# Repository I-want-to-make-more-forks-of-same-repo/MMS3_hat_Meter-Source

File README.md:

# MMS3 Hat Meter Source

## Sekcja 1: Dokumentacja Hat'a

### Krótki opis projektu
Hat meter-source to hat z woltomierzem, amperemoierzem, źródłem prądowym, napięciowym, obciążeniem napięciowym, prądowym (i pewnie też mocowym) na 1 kanale. Aktualnie płytka ma na celu przetestowanie konceptu i jest prototypem

### Zgodność ze standardem ChainBus

* ✅ Używa złącza ChainBus, nie zmienia jego miejsca ani pinoutu.
* ✅ Używa wyłącznie interfejsów I2C, SPI lub UART i nie inicjuje samodzielnie nowych transmisji (Nie jest master'em I2C albo SPI).
* ✅ Spełnia wymagania mechaniczne standardu (wymiary PCB, rozstaw otworów).
* ✅ Pobiera maksymalny prąd zgodny z ilością na jednego hat'a **-> Ma złącze XT60**
* ❌ Obsługuje napięcie wejściowe BRD_VIN do wartości 48V. **-> 12V max**

### Komunikacja i adresowanie

#### Magistrala Chainbus  I2C
Poniższa tabela przedstawia adresację urządzeń na magistrali I2C.

| Układ (IC)   | Funkcja                 |     Address     |
| :----------- | :---------------------- | :-------------: |
| **CH32V003** | Główny kontroler płytki | `Programowalny` |

#### Magistrala Chainbus SPI
Brak

#### Magistrala Chainbus UART
Brak

### Pinout złączy

| Jn     | Co                              | Jaki pin co robi                        |
| :----- | :------------------------------ | :-------------------------------------- |
| **J6** | Wyjście/wejście miernika/źródła | Pin 1: + <br>Pin 2: -                   |
| **J8** | TX UART z CH32V003              | Pin 1: TX (nazwany: free) <br>Pin 2: 0V |

Okay, i będe nazywał Pin + z J6 jako "Obciążenie" albo "Źródło" albo "Wejście" w dalszej części dokumentacji. To jest ten główny element tej płytki

### Wzmacniaczne operacyjne
Na płytce są użyte 4 wzmacniacze operacyjne

#### OpAmp Amperomierzy Wzmocniania Główny (OpAmp Amperomierzy)
Na schemacie to U3 kanał 1

| Pin  | Do czego podłączony                   |
| :--- | :------------------------------------ |
| +    | Wybrany bocznik prądowy (Sink/Source) |
| -    | Programowalny Rezystor Feedback       |
| OUT  | Amm_ADC (CH32 PD3)                    |

Programowalne wzmocnienie k

k = 31, jeśli Amm_Range_1 == 0

k = 70, jeśli Amm_Range_1 == 1

#### OpAmp Wzmocnienia amperomierza dla Mosfetów (OpAmp AmmMos)
Na schemacie to U6 kanał 1

| Pin  | Do czego podłączony                       |
| :--- | :---------------------------------------- |
| +    | Wybrany bocznik prądowy (Sink/Source)     |
| -    | Stały Rezystor Feedback                   |
| OUT  | Mosfet_Feedback jeśli Sel_Output_amm == 1 |

Stałe wzmocnienie = 11

Note: Wybrany bocznik prądowy jest ten sam dla obu OpAmp'ów. Nie możesz mieć jednego na jednym i drugiego na drugim

Note: Oba boczniki prądowe mają 20mΩ

#### OpAmp Mosfeta N
Na schemacie to U3 kanał 2

| Pin  | Do czego podłączony |
| :--- | :------------------ |
| +    | PWM_N z filtrem RC  |
| -    | Mosfet_Feedback     |
| OUT  | Bramka NMos'a       |

#### OpAmp Mosfeta P
Na schemacie to U7 kanał 2

| Pin  | Do czego podłączony |
| :--- | :------------------ |
| +    | Mosfet_Feedback     |
| -    | PWM_P z filtrem RC  |
| OUT  | Bramka PMos'a       |

Mosfet'y P są logicznie odwrócone od N, dlatego  mają na odwrót podłączenia + -

### Pinout CH32
| Pin            | Net name z kicad'a   | Co robi                                                                                      |
| :------------- | :------------------- | :------------------------------------------------------------------------------------------- |
| **PC0**        | PWM_P                | Sygnał PWM do wejścia OpAmp'a PMos'a                                                         |
| **PC1 (SDA)**  | N/A                  | SDA do ChainBus'a                                                                            |
| **PC2 (SCL)**  | N/A                  | SCL do ChainBus'a                                                                            |
| **PC3**        | Sel_Output_amm       | Wybór sprzężenia zwrotnego OpAmp'a PMos i Nmos - Na wyjście OpAmp'a AmmMos                   |
| **PC4**        | Sel_Output_Volt      | Wybór sprzężenia zwrotnego OpAmp'a PMos i Nmos - Na dzielnik napięcia 0.2 * Napięcie wejścia |
| **PC5 (SCK)**  | Amm_Range_1          | Wybór programowalnego wzmocnianie OpAmp'a Amperomierzy                                       |
| **PC6 (MOSI)** | Sel_Amp_Source       | Wybór wejscia dla OpAmp AmmMos i Amperomierzy na prąd wchodzący do pinu '+' Wejścia (Source) |
| **PC7 (MISO)** | Sel_Amp_Sink         | Wybór wejscia dla OpAmp AmmMos i Amperomierzy na prąd wychodzący z pinu '+' Wejścia (Sink)   |
| **PD0**        | Volt_Range1          | Wybór programowalnego dzielnika napięcia dla Volt_ADC                                        |
| **PD1**        | N/A                  | SWIO, programowanie MCU                                                                      |
| **PD2**        | PWM_N                | Sygnał PWM do wejścia OpAmp'a NMos'a                                                         |
| **PD3**        | Amm_ADC              | Kanał ADC połączony z wyjściem OpAmp'a Amperomierzy                                          |
| **PD4**        | Volt_ADC             | Kanał ADC połączony z programowalnym dzielnikiem napięcie Wejścia                            |
| **PD5 (TX)**   | Free                 | Wolny pin, do użycia jako dioda debug lub TX UART'a CH32V003                                 |
| **PD6 (RX)**   | Lmao1                | Wybór sprzężenia zwrotnego OpAmp'a - Na stałe 1.65V                                          |
| **PD7 (NRST)** | *NC (niepodłączony)* | NC                                                                                           |

Note: żeby Sel_Output_Volt, Sel_Output_amm i lmao1 działały potrzeba zewrzeć odpowiednio zworki J9 J10 J11

Note: Zwieraj je jedna na raz, bo jak kilka zewrzesz na Mosfet_Feedback będzie takie jak na najwyższym napięciu z podłączonych zworek

### Konfiguracja układu (Zworki/Rezystory)

| Co      | Jak podłączone                    | Efekt                                                                                             |
| :------ | :-------------------------------- | :------------------------------------------------------------------------------------------------ |
| **R15** | R15 Wylutowane <br> R15 Wlutowane | J6 '-' niepodłączony <br> J6 '-' podłączony do GND                                                |
| **R16** | R16 Wylutowane <br> R16 Wlutowane | Bramka Pmos'a podłączona do VIN_ChainBus <br> Bramka Pmos'a podłączona do wyjścia swojego OpAmp'a |
| **R26** | R26 Wylutowane <br> R26 Wlutowane | Bramka Nmos'a podłączona do 0V <br> Bramka Nmos'a podłączona do wyjścia swojego OpAmp'a           |
| **R27** | R27 Wylutowane <br> R27 Wlutowane | Dolna część mostka H odłączona <br> Dolna część mostka H podłączona do GND                        |
| **R29** | R29 Wylutowane <br> R29 Wlutowane | Wejście '-' OpAmp'a NMos'a floating <br> Wejście '-' OpAmp'a NMos'a podłączone do Mosfet_Feedback |
| **R30** | R30 Wylutowane <br> R30 Wlutowane | Wejście '+' OpAmp'a NMos'a floating <br> Wejście '+' OpAmp'a NMos'a podłączone do PWM_N przez RC  |
| **R32** | R32 Wylutowane <br> R32 Wlutowane | Wejście '-' OpAmp'a PMos'a floating <br> Wejście '-' OpAmp'a PMos'a podłączone do PWM_P przez RC  |
| **R42** | R42 Wylutowane <br> R42 Wlutowane | Wejście '+' OpAmp'a PMos'a floating <br> Wejście '+' OpAmp'a PMos'a podłączone do Mosfet_Feedback |
| **J9**  | J9 Rozwarte <br> J9 Zwarte        | Sel_Output_Volt nie działa jest elektrycznie odłączone <br> Można używać Sel_Output_Volt          |
| **J10** | J10 Rozwarte <br> J10 Zwarte      | Sel_Output_amm nie działa jest elektrycznie odłączone <br> Można używać Sel_Output_amm            |
| **J11** | J11 Rozwarte <br> J11 Zwarte      | Lmao1 nie działa jest elektrycznie odłączone <br> Można używać Lmao1                              |

Bascially rezystorów nie trzeba ruszać, chyba że chcesz wyłączyć któraś połowe mostka H, a zworki chcesz mieć tylko jedną na raz podpiętą jak zaczynasz programować.

### Szczegółowy opis
Na Hat'ie jest
- 1 Kanał woltomierza o programowalnym dzielniku napięcia
- 1 Kanał amperomierza o programowalnym wzmocnieniu oraz wybieralnym wejściu (między mierzeniem prądu sink a source)
- 1 Półmostek H

Do złącza J6 można podłączyć obciążenie/źródło i mierzyć prąd/napięcie na nim lub zasilać/obciążać go programowalnie. Minus (pin 1) tego złacza jest zwarty do masy układu, a plus (pin 2) jest podłączony do półmostka H.

Można mierzyć napięcie na **Wejściu** (J6 Pin 2). Napięcie **Wejścia** jest podłączone przez programowalny dzielnik napięciea do kanału ADC CH32V003 (Volt_ADC, PD4). Programowalny dzielnik napięcie zmienia się przez konfiguracje Volt_Range1

| Stan Volt_Range1 | napięcie na Volt_ADC        |
| :--------------- | :-------------------------- |
| High             | 0.2 * Napięcie Wejściowe    |
| Low              | 0.4285 * Napięcie Wejściowe |

Można mierzyć prąd na **Wejściu**. W tym celu na początku należy wybrać który prąd chcemy mierzyć
- Sel_Amp_Source - Prąd który płynie od '-' wyjścia do GND (Do amperomierza, i programowalnego źródła)
- Sel_Amp_Sink - Prąd który płynie od +, przez Mostek H do GND (Do Programable load)

Tryb pomiaru prądu (Sink, Source) jest wybrany dla pomiaru prądu przez mikrokontroler oraz dla OpAmp AmmMos (Sprzęrzenia zwrotnego OpAmp'ów Mosfetów). Pomiar prądu odbywa się przez rezystory 20mΩ. Napięcie na tym rezystorze jest wzmocnione. OpAmp AmmMos ma stałe wzmocnienie = 11 a mikrokontroler programowalne przez Amm_Range_1.

| Stan Amm_Range_1 | napięcie na Amm_ADC |
| :--------------- | :------------------ |
| High             | 71 * Prąd * 0.02    |
| Low              | 31 * Prąd * 0.02    |

Sterowanie półmostkiem H odbywa się pośrednio przez PWM z mikrokontrolera. Pośrednio, bo PWM jest wygładzane filtrem RC i idzie do wzmacniacza operacyjnego. Tak to wygląda:

PWM z MCU (PWM_N albo PWM_H) -> Filtr dolnoprzepustowty RC który z PWM robi stałe napięcie = 3.3 * % PWM -> Feedback Op Amp'a

Wzmacniacz operacyjny porównuje to wygładzone PWM z jedną z kilku programowo wybieranych opcji (Sel_Output_Volt, Sel_Output_amm, Lmao1) W celu zaimplementowanie closed loop control

| Co ma HIGH      | Do czego podpięty jest Mosfet_Feedback | Co można zaimplementować              |
| :-------------- | :------------------------------------- | ------------------------------------- |
| Sel_Output_Volt | 0.2 *          Napięcie Wejściowe      | Constant voltage source/sink          |
| Sel_Output_amm  | 11 * Prąd * 0.02                       | Constant current source/sink          |
| Lmao1           | 1.65V                                  | Sam amperomierz/woltomierz. Debugging |

Filtr RC składa się z 1kΩ i 1uF

Wszystkie Piny CH32V003 zostały wyprowadzone na Led'y w celu ułatwienia debuggowania. Oby to nie sprawiło problemów bo przez to są weak pulldown

### Tryby pracy
Jeśli jesteś programistą, to spoko gdyby udało ci się coś takiego zaimplementować

- Mierzenie napięcia
- Mierzenie prądu
- Źródło Prądowe
- Źródło Napięciowe
- Programowalne obciążenie Prądowe
- Programowalne obciążenie Napięciowe
- Programowalne obciążenie Mocowe

Która z tych opcji jest wybrana, wartości zmierzone albo nastawy muszą być konfigurowalne z poziomu MMS3, a nie Hat'a. I fajnie gdyby był jeden program na CH32 na wszystkie te tryby (One soft to rule them all ;)

I trzeba napisać oba: Software na CH32V003 i biblioteke hat'a żeby to działało ze sobą. Jak masz problem z CH32 to możesz debuggować WCH-Link'iem albo prinf'em (TX -> UART/USB przejściówka -> PC)

### Gotowe arkusze hierarchiczne
W projekcie zaprojektowano/użyto następujących arkuszy hierarchicznych:
* CH32V003

---

## Sekcja 2: Specyfikacja standardu ChainBus

### Architektura i łączenie modułów
Standard ChainBus umożliwia modułowe łączenie hatów. Na jednym MMS3 można zamontować pionowo **do 8 hat'ów**. Połączenie realizowane jest poprzez wpięcie złącza męskiego kolejnego hat'a w złącze żeńskie poprzedniego

### Komunikacja i sterowanie
Magistrala ChainBus jest w pełni cyfrowa. Płyta główna nie steruje bezpośrednio sygnałami ogólnego przeznaczenia (GPIO) na poszczególnych hat'ach. Wszelkie operacje (np. obsługa diod LED, odczyt krańcówek, generowanie sygnałów PWM) muszą być realizowane przez dedykowane układy scalone (np. ekspandery portów, sterowniki) komunikujące się przez interfejsy systemowe.

*Przykład:*
`MCU` $\rightarrow$ `Expander GPIO po I2C` $\rightarrow$ `Dioda LED`

Wybór aktywnego modułu realizowany jest przez układ przełącznika magistrali (bus switch) na płycie głównej. Dzięki temu linie I2C, SPI i UART są niezależne dla każdego hat'a (brak konfliktów adresów I2C między różnymi hatami).
* **Identyfikacja:** Każdy moduł powinien posiadać pamięć EEPROM na magistrali I2C w celu identyfikacji płyty przez system - układ M24C64-W skonfigurowany na adres `0x50` przy liniach adresowych A0, A1, A2 zwartych do masy.

### Zasilanie
Złącze ChainBus dostarcza następujące linie zasilania:

| Magistrala zasilania | Napięcie znamionowe | Maksymalny prąd (łączny dla 8 hatów) | Szacowany prąd na jeden hat |
| :------------------- | :-----------------: | :----------------------------------: | :-------------------------: |
| **5V**               |        5.0 V        |                1.0 A                 |           125 mA            |
| **12V stby**         |       12.0 V        |                0.5 A                 |            65 mA            |
| **BRD_VIN**          |   12.0 V – 48.0 V   |                1.5 A                 |           185 mA            |

*   Komponenty podłączone do linii `BRD_VIN` muszą być przystosowane do pracy z napięciem od 12V do **48 V**.
*   W przypadku zapotrzebowania na wyższą moc, dopuszczalne jest zastosowanie dodatkowego złącza zasilania XT60 (obciążalność do ok. 60 A).

### Wymagania mechaniczne i złącza
* **Wymiary PCB:** Niedozwolona jest zmiana obrysu płytki oraz położenia otworów montażowych, aby zachować kompatybilność mechaniczną.
* **Pozycjonowanie złączy ChainBus:** Położenie złącza standardu 2x16 SMD (raster 2.54 mm) musi być zgodne z szablonem. Złącze żeńskie montowane jest na stronie FRONT, natomiast złącze męskie na stronie BACK.
* **Interfejsy zewnętrzne:** Złącza wejścia/wyjścia (domyślnie standard JST-XH 2.5 mm o obciążalności do 3 A) oraz opcjonalne złącze XT60 powinny być umieszczone przy dolnej krawędzi płytki. Elementy regulacyjne i sygnalizacyjne (potencjometry, przełączniki, diody LED) należy lokalizować przy prawej krawędzi płytki.
* **Komponenty** Wszystkie komponenty powinny być na stronie front płytki żeby nie haczyły o elementy ze wcześniejszego hat'a

---

## Sekcja 3: Licencje

### Licencje projektu

*   **PCB:** CERN-OHL-P
*   **Software:** MIT License

[Template](https://github.com/KoNaR-Hefajstos/MMS3_hat_templates/) jest na licencji CC0 1.0 Universal. **Reszta projektu nie jest na tej licencji**

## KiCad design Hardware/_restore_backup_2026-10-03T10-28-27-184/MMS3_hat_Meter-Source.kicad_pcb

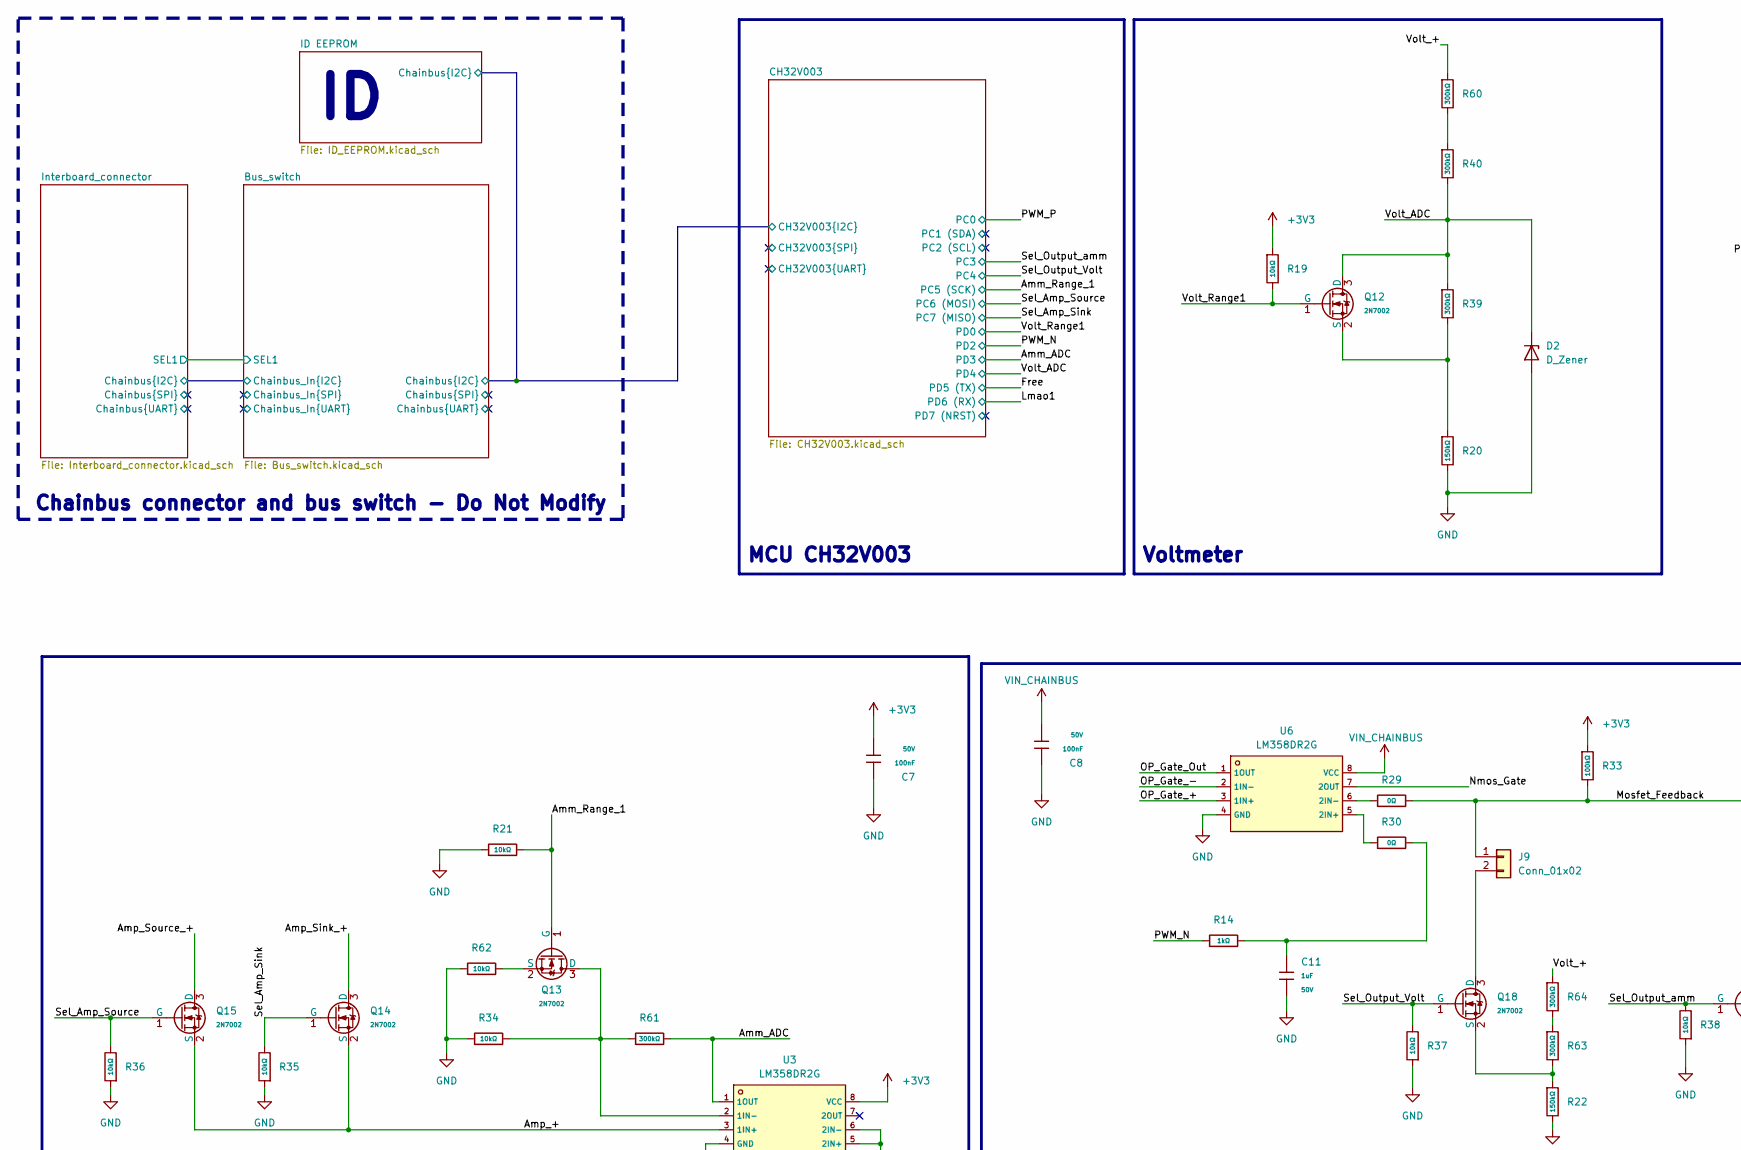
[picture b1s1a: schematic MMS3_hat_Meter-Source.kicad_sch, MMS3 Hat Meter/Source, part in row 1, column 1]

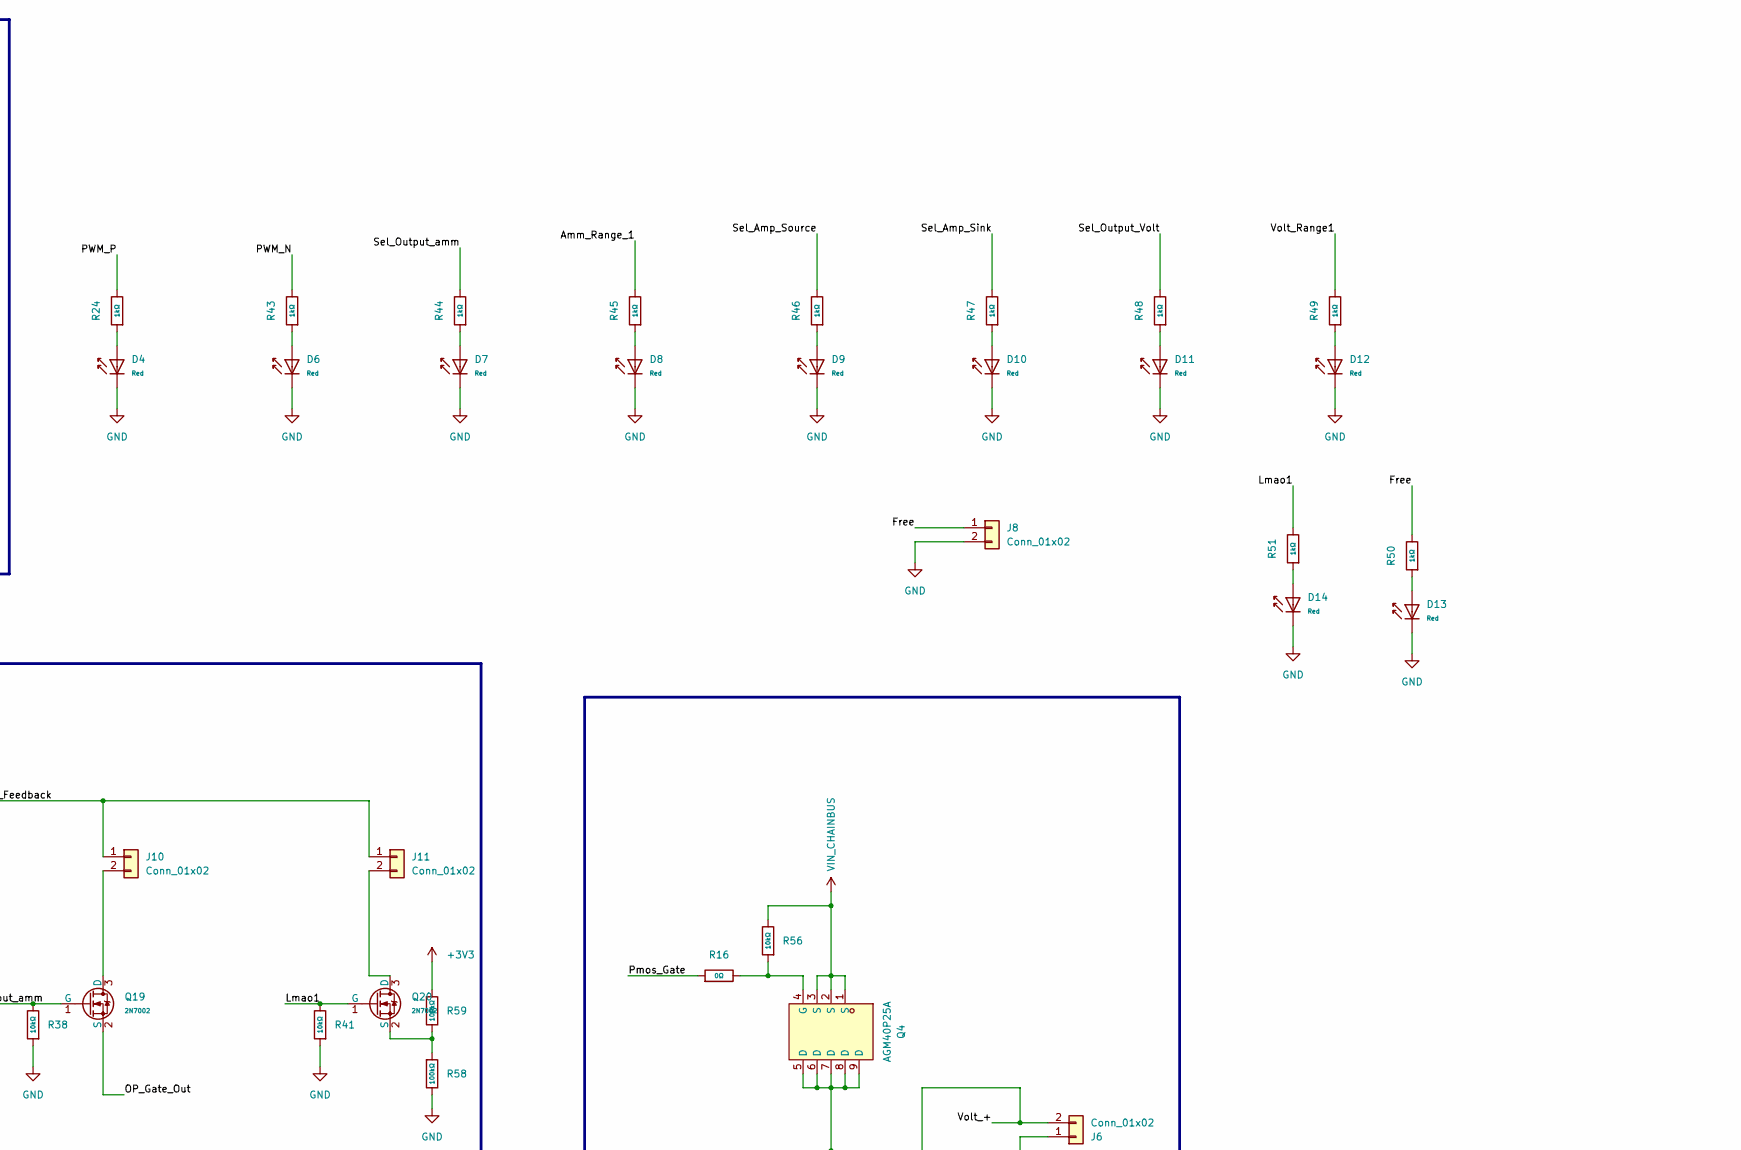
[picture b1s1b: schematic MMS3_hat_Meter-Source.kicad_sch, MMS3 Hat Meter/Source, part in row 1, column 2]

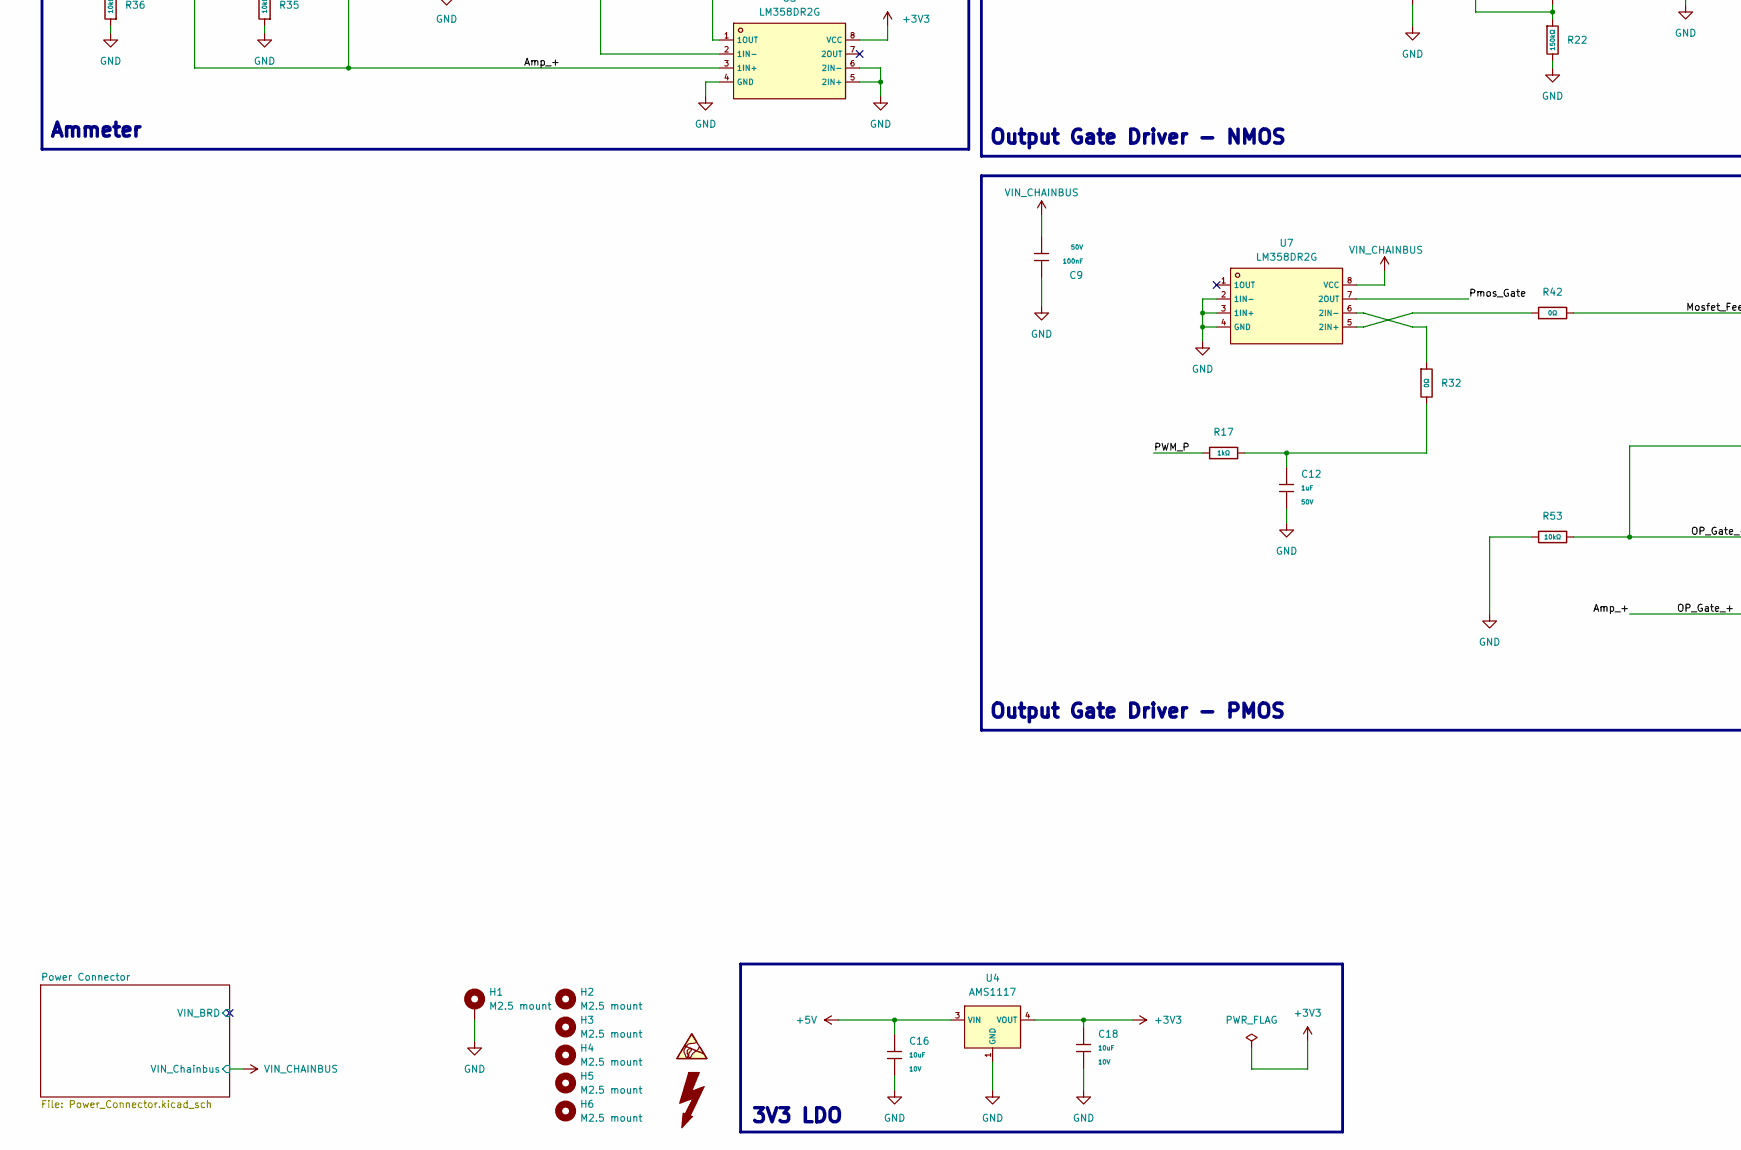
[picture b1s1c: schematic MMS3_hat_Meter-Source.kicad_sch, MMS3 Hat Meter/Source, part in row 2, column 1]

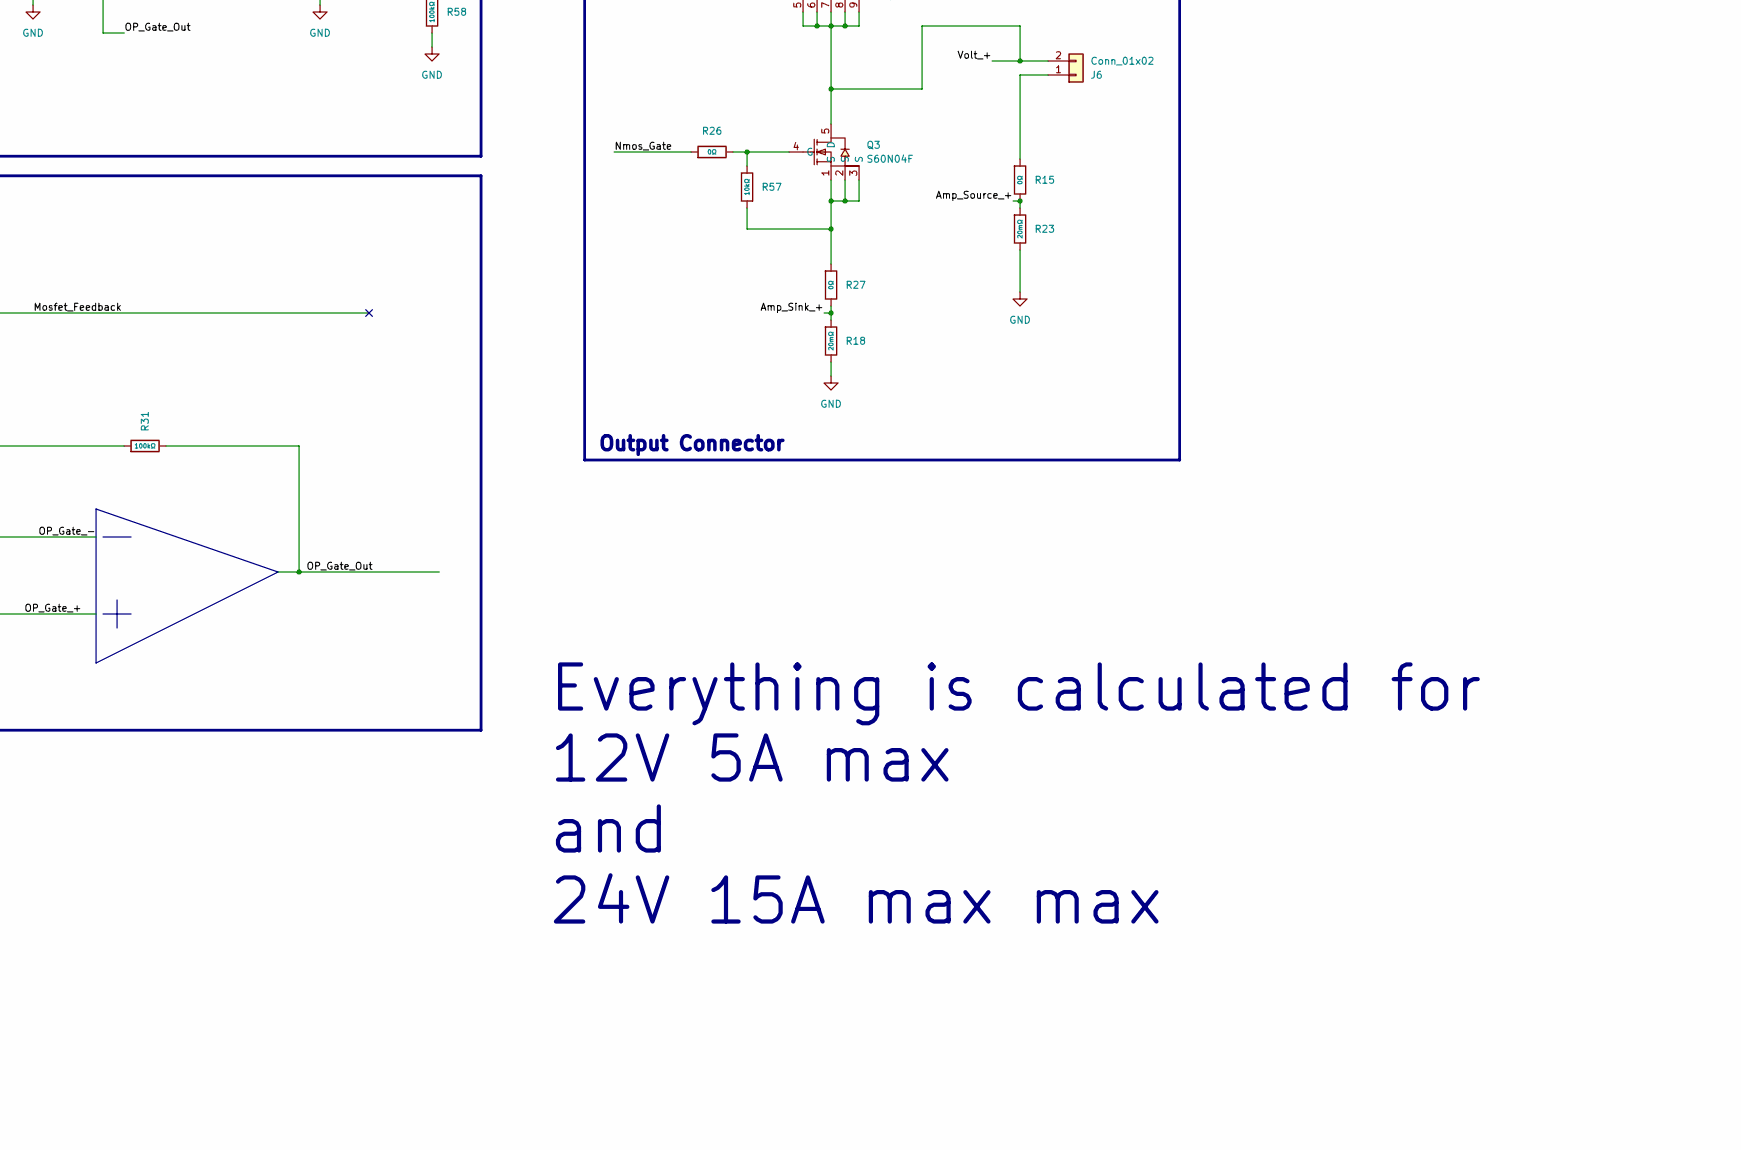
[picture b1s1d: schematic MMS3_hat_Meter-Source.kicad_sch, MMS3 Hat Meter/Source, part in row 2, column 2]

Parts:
C7, C8, C9: 100nF; C_0603; Voltage Rated 50V; Tolerance ±10%; Part CC0603KRX7R9BB104; LCSC C14663
C11, C12: 1uF; C_0603; Voltage Rated 50V; Tolerance ±10%; Part CL10A105KB8NNNC; LCSC C15849
C16, C18: 10uF; C_0603; Voltage Rated 10V; Tolerance ±10%; Part CL10A106KP8NNNC; LCSC C19702
D2: D_Zener; D_0603
D4, D6, D7, D8, D9, D10, D11, D12, D13, D14: Red; D_0603; Part KT-0603R; LCSC C2286
H1: M2.5 mount; MountingHole_2.7mm_M2.5_DIN965_Pad_TopOnly
H2, H3, H4, H5, H6: M2.5 mount; MountingHole_2.7mm_M2.5
J6: Conn_01x02; JST_XH_S2B-XH-A_1x02_P2.50mm_Horizontal
J8: Conn_01x02; JST_XH_B2B-XH-A_1x02_P2.50mm_Vertical
J9, J10, J11: Conn_01x02; PinHeader_1x02_P2.54mm_Vertical
Q3: S60N04F; DFN-5_L4.9-W5.9-P1.27-LS6.2-BL; MPN S60N04F; LCSC Part C7543820
Q4: AGM40P25A; PDFN-8_L5.8-W5.0-P1.27-LS6.1-BL; MPN AGM40P25A; LCSC Part C22386140
Q12, Q13, Q14, Q15, Q18, Q19, Q20: 2N7002; Q_SOT-23; Part 2N7002; LCSC C8545
R14, R17, R24, R43, R44, R45, R46, R47, R48, R49, R50, R51: 1kΩ; R_0603; Overload Voltage (Max) 75V; Tolerance ±1%; Part 0603WAF1001T5E; LCSC C21190
R15, R16, R26, R27, R29, R30, R32, R42: 0Ω; R_0603; Overload Voltage (Max) 75V; Tolerance ±1%; Part 0603WAF0000T5E; LCSC C21189
R18, R23: 20mΩ; R_0603; Overload Voltage (Max) 75V; Tolerance ±1%; Part 0603WAF100KT5E
R19, R21, R34, R35, R36, R37, R38, R41, R53, R56, R57, R62: 10kΩ; R_0603; Overload Voltage (Max) 75V; Tolerance ±1%; Part 0603WAF1002T5E; LCSC C25804
R20, R22: 150kΩ; R_0603; Overload Voltage (Max) 75V; Tolerance ±1%; Part 0603WAF1503T5E; LCSC C22807
R31, R33, R58, R59: 100kΩ; R_0603; Overload Voltage (Max) 75V; Tolerance ±1%; Part 0603WAF1003T5E; LCSC C25803
R39, R40, R60, R61, R63, R64: 300kΩ; R_0603; Overload Voltage (Max) 75V; Tolerance ±1%; Part 0603WAF3003T5E; LCSC C23024
U3, U6, U7: LM358DR2G; SOIC-8_L5.0-W4.0-P1.27-LS6.0-BL; Part LM358DR2G; LCSC C7950
U4: AMS1117; SOT-223-3_L6.5-W3.4-P2.30-LS7.0-BR; Output Voltage 3.3V; Dropout Voltage 1.3V@(800mA); Part AMS1117-3.3; LCSC C6186

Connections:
+3V3: C7.1, C18.1, R19.1, R33.1, R59.1, U3.8 (VCC), U4.2 (VOUT), U4.4 (VOUT); also elsewhere on the board
+5V: C16.1, U4.3 (VIN); also elsewhere on the board
/Amm_ADC: R61.2, U3.1 (1OUT); also elsewhere on the board
/Amm_Range_1: Q13.1 (G), R21.2, R45.2; also elsewhere on the board
/Amp_+: Q14.2 (S), Q15.2 (S), U3.3 (1IN+), U6.3 (1IN+)
/Amp_Sink_+: Q14.3 (D), R18.1, R27.2
/Amp_Source_+: Q15.3 (D), R15.2, R23.1
/Free: J8.1, R50.2; also elsewhere on the board
/Lmao1: Q20.1 (G), R41.2, R51.2; also elsewhere on the board
/Mosfet_Feedback: J9.1, J10.1, J11.1, R29.2, R33.2, R42.2
/Nmos_Gate: R26.1, U6.7 (2OUT)
/OP_Gate_-: R31.1, R53.1, U6.2 (1IN-)
/OP_Gate_Out: Q19.2 (S), R31.2, U6.1 (1OUT)
/PWM_N: R14.1, R43.2; also elsewhere on the board
/PWM_P: R17.1, R24.2; also elsewhere on the board
/Pmos_Gate: R16.1, U7.7 (2OUT)
/Sel_Amp_Sink: Q14.1 (G), R35.2, R47.2; also elsewhere on the board
/Sel_Amp_Source: Q15.1 (G), R36.2, R46.2; also elsewhere on the board
/Sel_Output_Volt: Q18.1 (G), R37.2, R48.2; also elsewhere on the board
/Sel_Output_amm: Q19.1 (G), R38.2, R44.2; also elsewhere on the board
/Volt_+: J6.2, Q3.5 (D), Q4.5 (D), Q4.6 (D), Q4.7 (D), Q4.8 (D), Q4.9 (D), R60.1, R64.1
/Volt_ADC: D2.1 (K), Q12.3 (D), R39.1, R40.2; also elsewhere on the board
/Volt_Range1: Q12.1 (G), R19.2, R49.2; also elsewhere on the board
GND: C7.2, C8.2, C9.2, C11.2, C12.2, C16.2, C18.2, D2.2 (A), D4.1, D6.1, D7.1, D8.1, D9.1, D10.1, D11.1, D12.1, D13.1, D14.1, H1.1 (1_1), J8.2, R18.2, R20.2, R21.1, R22.2, R23.2, R34.1, R35.1, R36.1, R37.1, R38.1, R41.1, R53.2, R58.2, R62.1, U3.4 (GND), U3.5 (2IN+), U3.6 (2IN-), U4.1 (GND), U6.4 (GND), U7.2 (1IN-), U7.3 (1IN+), U7.4 (GND); also elsewhere on the board
unnamed: C11.1, R14.2, R30.2
unnamed: C12.1, R17.2, R32.2
unnamed: D4.2, R24.1
unnamed: D6.2, R43.1
unnamed: D7.2, R44.1
unnamed: D8.2, R45.1
unnamed: D9.2, R46.1
unnamed: D10.2, R47.1
unnamed: D11.2, R48.1
unnamed: D12.2, R49.1
unnamed: D13.2, R50.1
unnamed: D14.2, R51.1
unnamed: J6.1, R15.1
unnamed: J9.2, Q18.3 (D)
unnamed: J10.2, Q19.3 (D)
unnamed: J11.2, Q20.3 (D)
unnamed: Q3.4 (G), R26.2, R57.2
unnamed: Q3.1 (S), Q3.2 (S), Q3.3 (S), R27.1, R57.1
unnamed: Q4.4 (G), R16.2, R56.1
unnamed: Q12.2 (S), R20.1, R39.2
unnamed: Q13.3 (D), R34.2, R61.1, U3.2 (1IN-)
unnamed: Q13.2 (S), R62.2
unnamed: Q18.2 (S), R22.1, R63.2
unnamed: Q20.2 (S), R58.1, R59.2
unnamed: R40.1, R60.2
unnamed: R63.1, R64.2
unnamed: R30.1, U6.5 (2IN+)
unnamed: R29.1, U6.6 (2IN-)
unnamed: R42.1, U7.5 (2IN+)
unnamed: R32.1, U7.6 (2IN-)
VIN_CHAINBUS: C8.1, C9.1, Q4.1 (S), Q4.2 (S), Q4.3 (S), R56.2, U6.8 (VCC), U7.8 (VCC); also elsewhere on the board

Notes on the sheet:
Ammeter
Output Gate Driver - NMOS
Voltmeter
Output Gate Driver - PMOS
Output Connector
Everything is calculated for 12V 5A max and 24V 15A max max
3V3 LDO
MCU CH32V003
Chainbus connector and bus switch - Do Not Modify

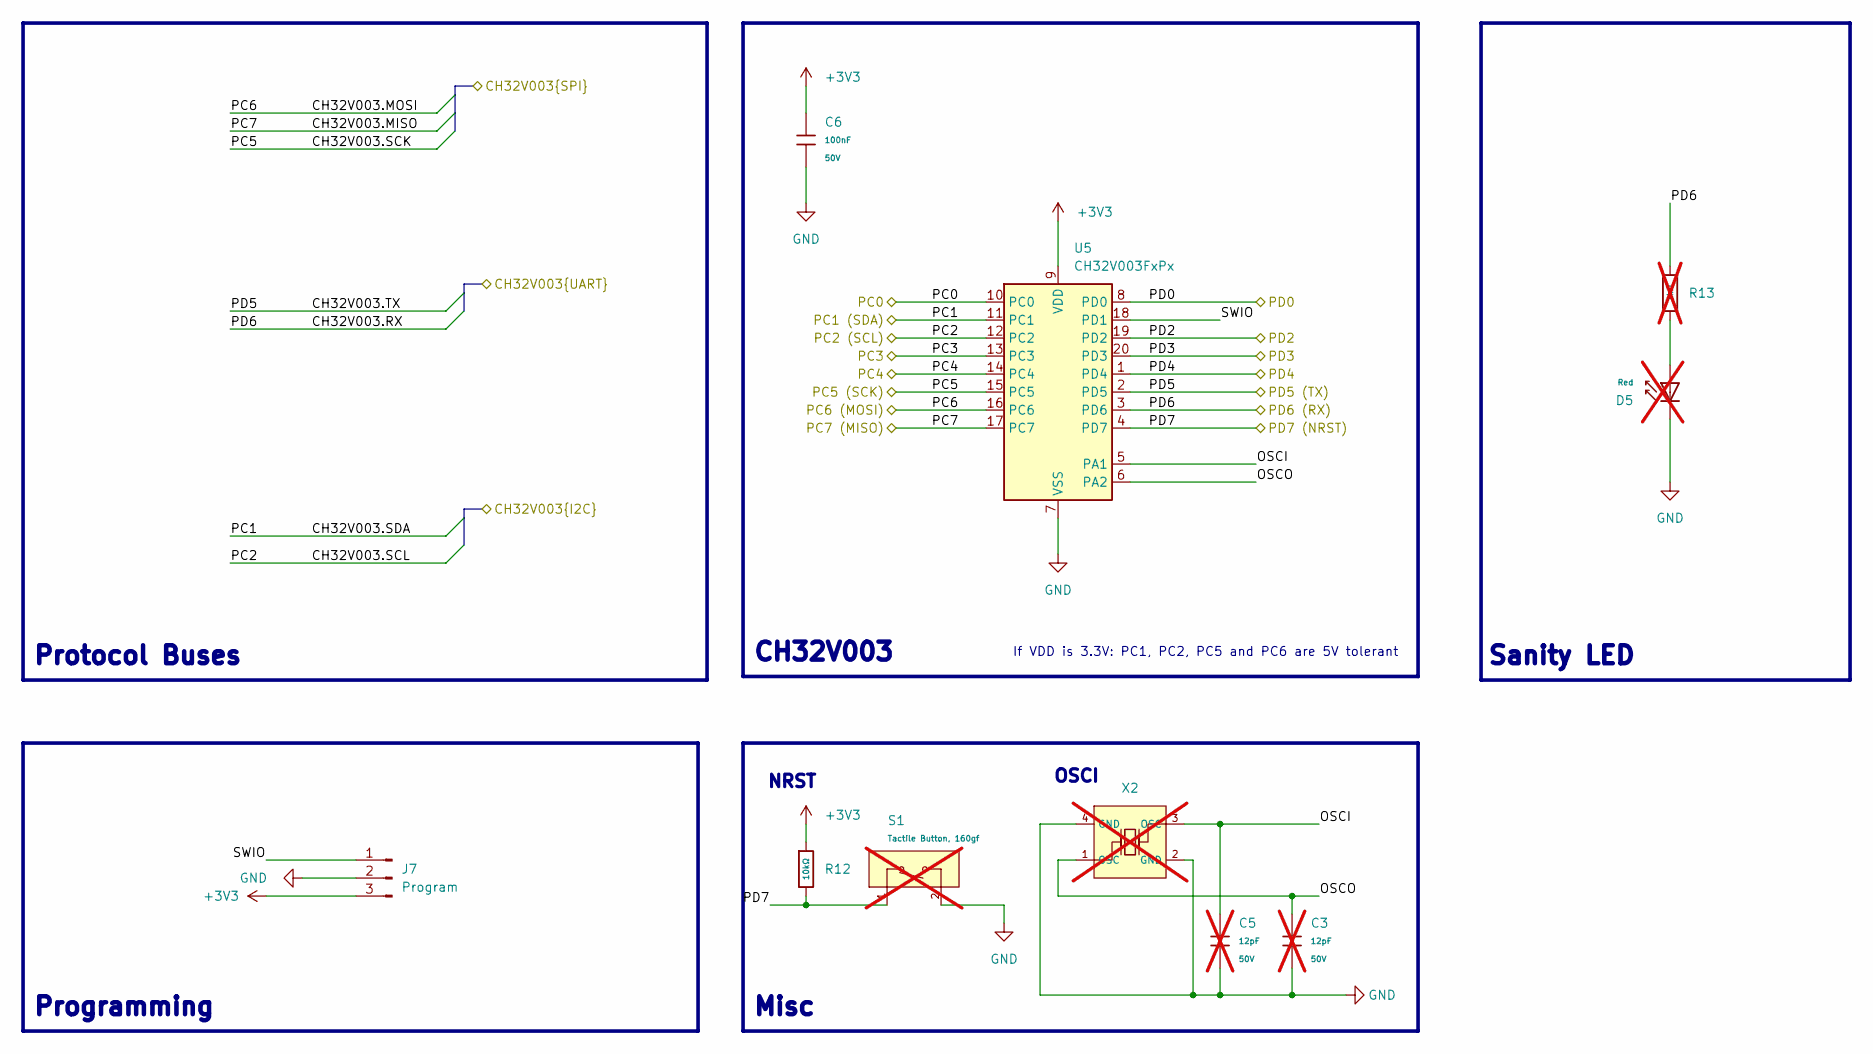
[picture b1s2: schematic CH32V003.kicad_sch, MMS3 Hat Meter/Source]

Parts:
C3, C5: 12pF; C_0603; Voltage Rated 50V; Tolerance ±5%; Part CL10C120JB8NNNC; LCSC C38523; not fitted
C6: 100nF; C_0603; Voltage Rated 50V; Tolerance ±10%; Part CC0603KRX7R9BB104; LCSC C14663
D5: Red; D_0603; Part KT-0603R; LCSC C2286; not fitted
J7: Program; PinHeader_1x03_P2.54mm_Vertical
R12: 10kΩ; R_0603; Overload Voltage (Max) 75V; Tolerance ±1%; Part 0603WAF1002T5E; LCSC C25804
R13: 1kΩ; R_0603; Overload Voltage (Max) 75V; Tolerance ±1%; Part 0603WAF1001T5E; LCSC C21190; not fitted
S1: Tactile Button, 160gf; SW_TS-1088-AR02016; Voltage Rating (Dc) 12V; Part TS-1088-AR02016; LCSC C720477; not fitted
U5: CH32V003FxPx; TSSOP-20_4.4x6.5mm_P0.65mm
X2: X322525MOB4SI; OSC-SMD_4P-L3.2-W2.5-BL; Frequency Tolerance ±10ppm; Part X322525MOB4SI; LCSC C9006; not fitted

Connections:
+3V3: C6.1, J7.3, R12.1, U5.9 (VDD); also elsewhere on the board
/Amm_ADC: U5.20 (PD3); also elsewhere on the board
/Amm_Range_1: U5.15 (PC5); also elsewhere on the board
/Bus_switch/Chainbus.SCL: U5.12 (PC2); also elsewhere on the board
/Bus_switch/Chainbus.SDA: U5.11 (PC1); also elsewhere on the board
/CH32V003/OSCI: C5.1, U5.5 (PA1), X2.3 (OSC)
/CH32V003/OSCO: C3.1, U5.6 (PA2), X2.1 (OSC)
/CH32V003/PD7: R12.2, S1.1 (A), U5.4 (PD7)
/CH32V003/SWIO: J7.1, U5.18 (PD1)
/Free: U5.2 (PD5); also elsewhere on the board
/Lmao1: R13.1, U5.3 (PD6); also elsewhere on the board
/PWM_N: U5.19 (PD2); also elsewhere on the board
/PWM_P: U5.10 (PC0); also elsewhere on the board
/Sel_Amp_Sink: U5.17 (PC7); also elsewhere on the board
/Sel_Amp_Source: U5.16 (PC6); also elsewhere on the board
/Sel_Output_Volt: U5.14 (PC4); also elsewhere on the board
/Sel_Output_amm: U5.13 (PC3); also elsewhere on the board
/Volt_ADC: U5.1 (PD4); also elsewhere on the board
/Volt_Range1: U5.8 (PD0); also elsewhere on the board
GND: C3.2, C5.2, C6.2, D5.1, J7.2, S1.2 (B), U5.7 (VSS), X2.2 (GND), X2.4 (GND); also elsewhere on the board
unnamed: D5.2, R13.2

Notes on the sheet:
NRST
Sanity LED
If VDD is 3.3V: PC1, PC2, PC5 and PC6 are 5V tolerant
CH32V003
OSCI
Protocol Buses
Misc
Programming

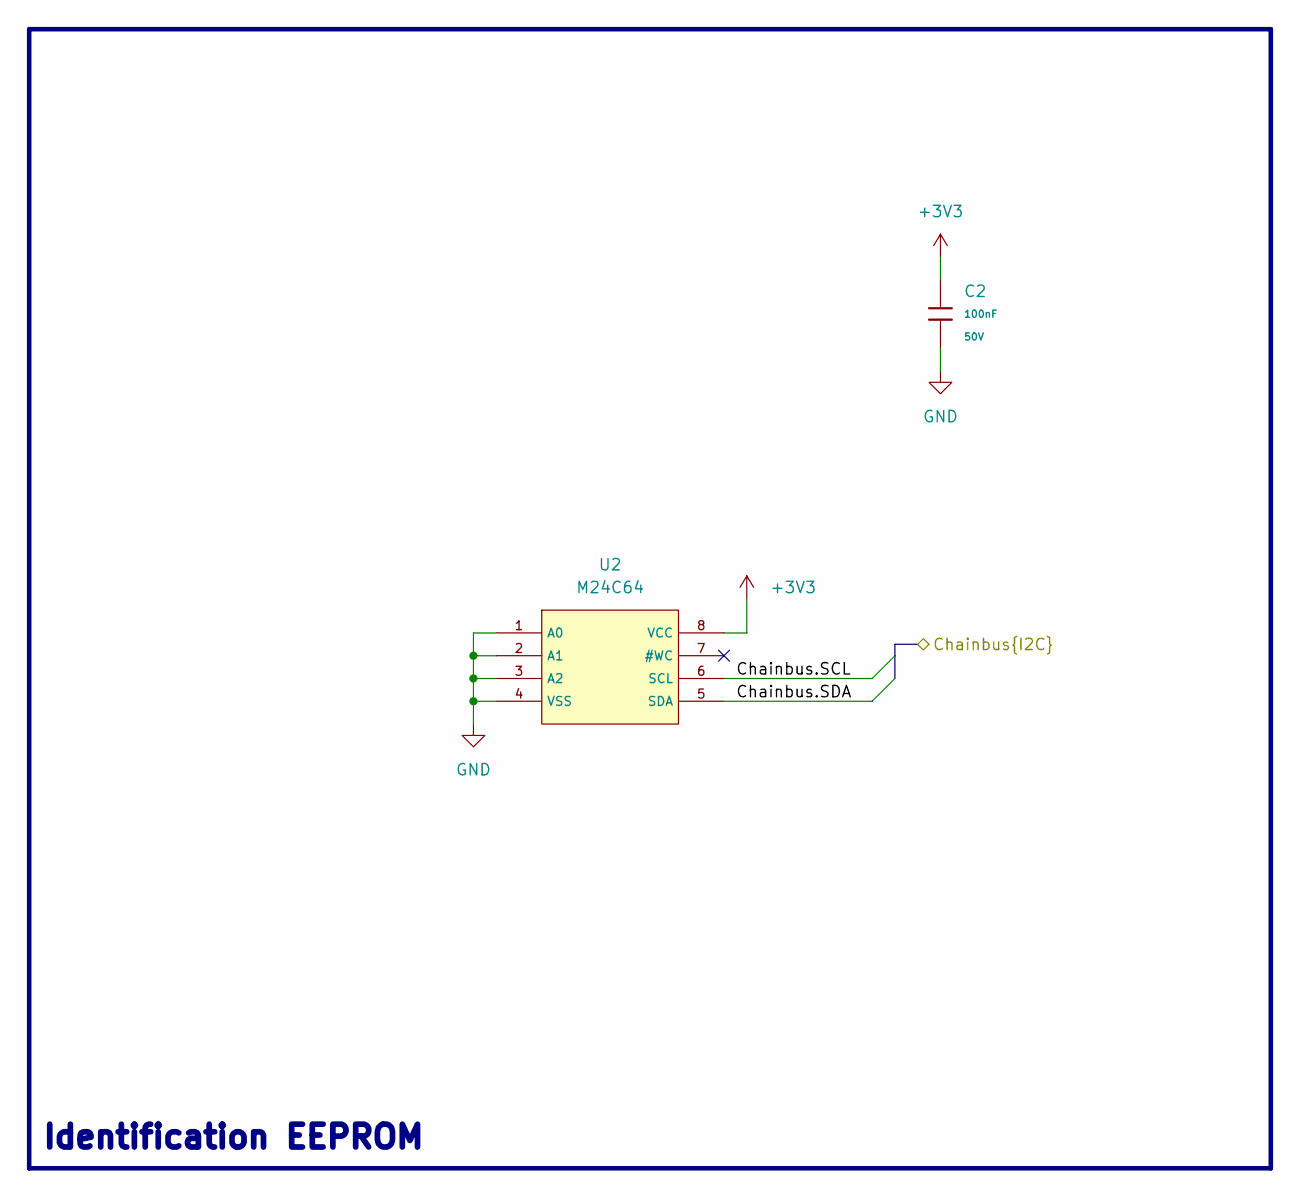
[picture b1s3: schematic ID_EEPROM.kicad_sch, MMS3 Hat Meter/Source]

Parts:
C2: 100nF; C_0603; Voltage Rated 50V; Tolerance ±10%; Part CC0603KRX7R9BB104; LCSC C14663
U2: M24C64; SOIC-8_L5.0-W4.0-P1.27-LS6.0-BL; Supply Voltage 1.8V~5.5V; Part M24C64-RMN6TP; LCSC C79988

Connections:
+3V3: C2.1, U2.8 (VCC); also elsewhere on the board
/Bus_switch/Chainbus.SCL: U2.6 (SCL); also elsewhere on the board
/Bus_switch/Chainbus.SDA: U2.5 (SDA); also elsewhere on the board
GND: C2.2, U2.1 (A0), U2.2 (A1), U2.3 (A2), U2.4 (VSS); also elsewhere on the board

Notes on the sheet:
Identification EEPROM
